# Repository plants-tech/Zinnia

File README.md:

# ZinniaGCC

fork of a fork of phob 2.x (Phob 2.x Official -> PhloraGCC -> ZinniaGCC)

RIP Jack Plants 

## Changes

* USB D+/D- Pad Alignment with [Model U GCC v2](https://github.com/plants-tech/Model-U-GCC-V2)
* Left Z implementation via its own pin; GPIO12
* Start Pad edit; now in style of D-Pad 
* B3f tactile switch thru-holes on ABXY pads
* Omron D2LS alignment thru-holes on ABXY pads (experimental)
* Revision of both Analog and C-Stick footprints; removal of t1/t2 thru-holes, conversion of t3 screw-holes from copper-lined pads to non-conductive thru-holes (screws work more effectively, stickbox "wobble" eliminated slightly)

## Images

### Front

### Back

## License

[CERN_OHL_S_v2](https://ohwr.org/cern_ohl_s_v2.txt)

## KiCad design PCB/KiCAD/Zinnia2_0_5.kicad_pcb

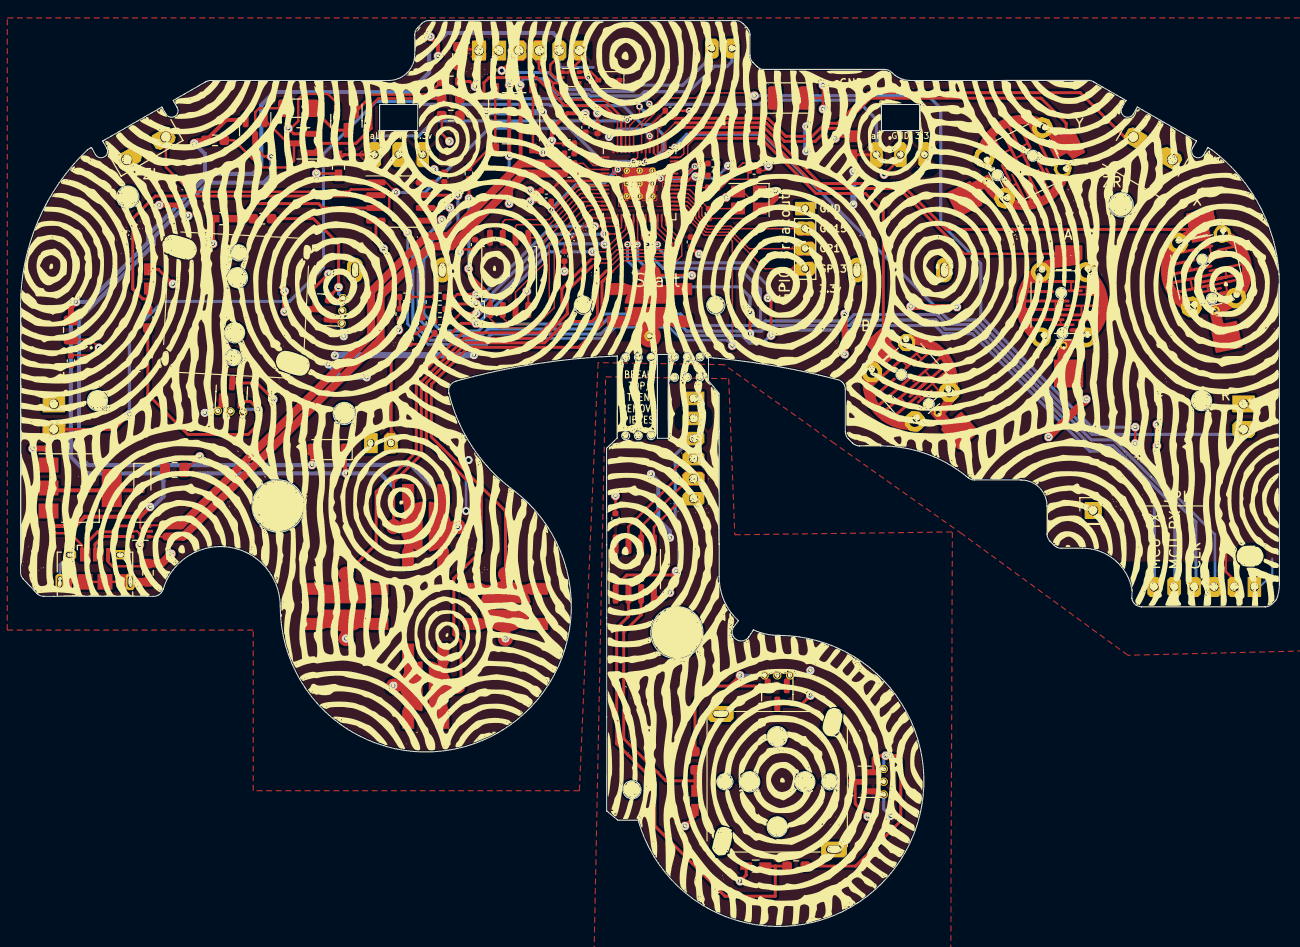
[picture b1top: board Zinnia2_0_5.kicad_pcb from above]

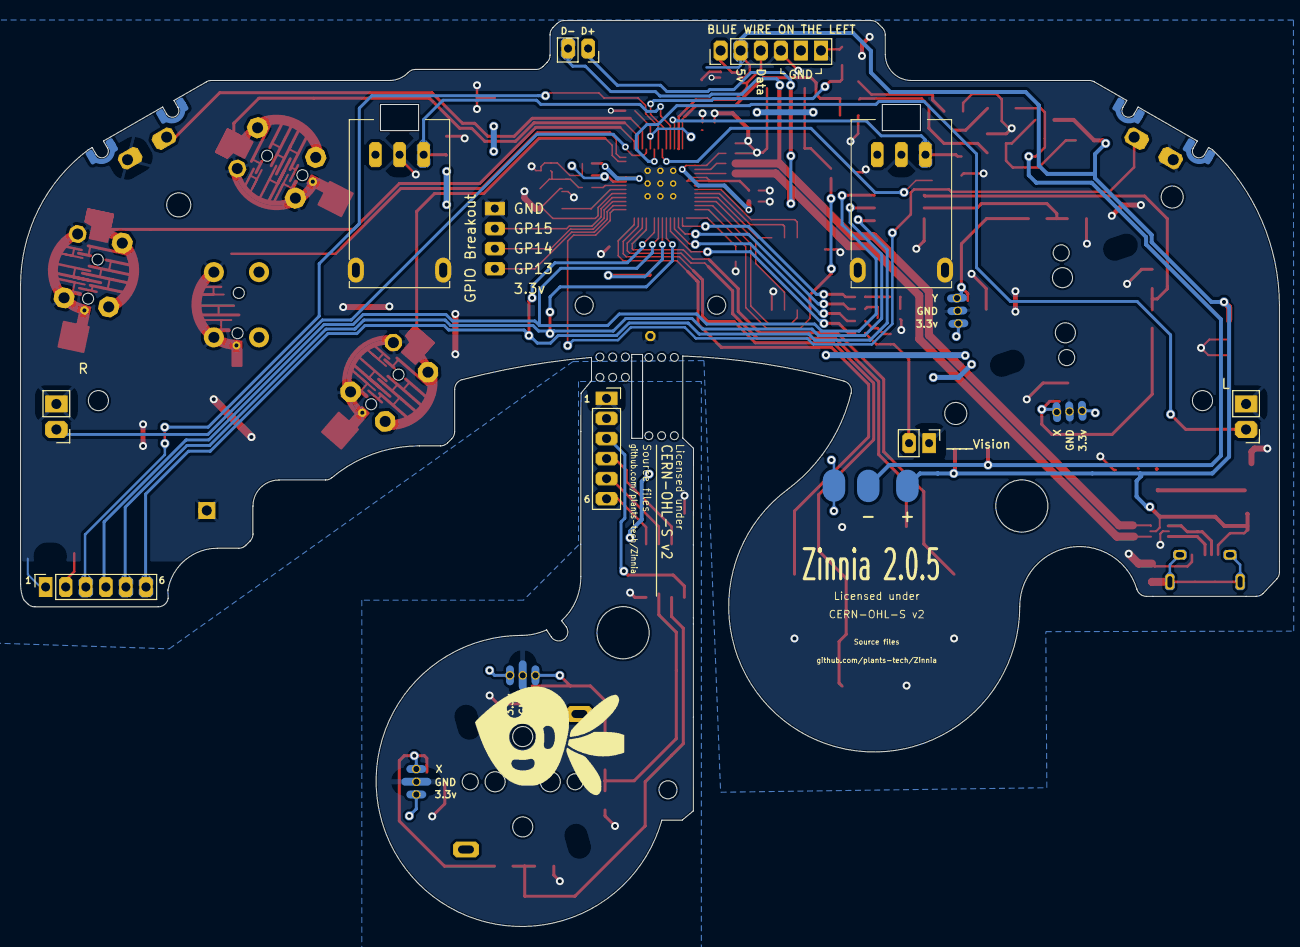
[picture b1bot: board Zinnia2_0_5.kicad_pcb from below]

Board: 2 copper layers, 125.4 x 90.3 mm, 110 parts (9 on the bottom side), 77 nets.

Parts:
C1: 47u; CP_EIA-3528-12_Kemet-T
C3, C4, C5, C6, C7, C8: 0.047u; C_0603_HandSoldering
C14, C15: 27p; C_0402_1005Metric
C16, C18: 10u; C_0805_2012Metric
C17, C19, C20, C22, C24, C25, C26, C27, C28, C29, C30, C31, C32: 100n; C_0402_1005Metric
C21, C23: 1u; C_0402_1005Metric
D1, D5: CUS10S30,H3F; D_SOD-323
D2: M7C; D_SOD-123
F1: Fuse; Fuse_1206_3216Metric
H1: 5.2mm; MountingHole_5.2mm
H2: Slot
H3, H4: 2mm; MountingHole_2.0mm
H5, H6: 1.8mm; MountingHole_1.8mm
H7: 2.4mm; MountingHole_2.4mm
H8, H9: 2.2mm; MountingHole_2.2mm
H10: MountingHole; MountingHole_1.8mm
H11: MountingHole; MountingHole_5.2mm
H12, H13: MountingHole; MountingHole_2.0mm
H14: MouseBite; breakaway-mousebites-double-v2-small
H15: MouseBite; breakaway-mousebites-double-v2-large
J1: Conn_01x06_Female; GCC_Header_Straight_1x06_Pitch2.00mm
J2, J11: Conn_01x02; PinHeader_1x02_P2.00mm_Vertical
J4: Conn_01x01; PinHeader_1x01_P2.54mm_Vertical
J5: Rumble; rumble_pins
J6: PinSocket_1x04_P2.00mm_Vertical
J9: USB_B_Micro; USB_Micro-B_Amphenol_10118194_Horizontal
J14, J15: Conn_01x06; PinSocket_1x06_P2.00mm_Vertical
Q1, Q3: Q_NMOS_GSD; SOT-23
Q2: Q_PMOS_GDS; SOT-23
R1, R2, R7, R8, R9: 180; R_0402_1005Metric
R3, R4, R5, R6: 2k; R_0603_1608Metric_Pad0.98x0.95mm_HandSolder
R10, R19, R24, R25: 316; R_0402_1005Metric
R11, R12: 100R; R_0603_1608Metric_Pad0.98x0.95mm_HandSolder
R13, R14, R15: 10k; R_0603_1608Metric_Pad0.98x0.95mm_HandSolder
R16, R18: 1k; R_0402_1005Metric
R17: 100k; R_0603_1608Metric_Pad0.98x0.95mm_HandSolder
R20, R21: 27; R_0402_1005Metric
RV1, RV2: R_POT_MountingPin; f
S1: BOOTSEL; SW_TS-1187A-B-A-B
SW1: A; ABXY_Contact_Omron_Switch_b3F_v2
SW2: B; ABXY_Contact_Omron_Switch_b3F_v2
SW3: X; ABXY_Contact_Omron_Switch_b3F_v2
SW4: Y; ABXY_Contact_Omron_Switch_b3F_v2
SW5: Start; Dpad_Contact_TL3315NF_2
SW6: L; Pin_Header_Straight_1x02_Pitch2.54mm
SW7: R; Pin_Header_Straight_1x02_Pitch2.54mm
SW8: Z; Z_Switch_Edge_Omron
SW8L: ZL; Z_Switch_Edge_Omron
SW9: Dleft; Dpad_Contact_TL3315NF_2
SW10: Dup; Dpad_Contact_TL3315NF_2
SW11: Dright; Dpad_Contact_TL3315NF_2
SW12: Ddown; Dpad_Contact_TL3315NF_2
U1, U3: MCP3002; SOIC-8_3.9x4.9mm_P1.27mm
U2: Stickbox_Assembly_Main; GCC_Stickbox_Hall_Only
U4, U9, U10, U11: DRV5055Z3QDBZT; SOT-23
U5: Stickbox_Assembly_CStick; GCC_Stickbox_Hall_Only
U6: AMS1117-3.3; SOT-223-3_TabPin2
U7: W25Q128JVS; SOIC-8_5.23x5.23mm_P1.27mm
U8: RP2040; RP2040-QFN-56
U12, U13: USBLC6-2P6; SOT-666
Y1: Crystal_GND24; Crystal_SMD_3225-4Pin_3.2x2.5mm

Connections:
+1V1: C19.1, C20.1, C21.1, U8.23 (DVDD), U8.45 (VREG_VOUT), U8.50 (DVDD)
+3V3: C1.1, C17.1, C18.1, C22.1, C23.1, C24.1, C25.1, C26.1, C27.1, C28.1, C29.1, C30.1, C31.1, D1.1 (K), D5.1 (K), J1.1, J14.2, RV1.1 (V+), RV2.1 (V+), U1.8 (VDD/VREF), U2.1 (H1XV), U2.4 (H1YV), U7.8 (VCC), U8.1 (IOVDD), U8.10 (IOVDD), U8.22 (IOVDD), U8.33 (IOVDD), U8.42 (IOVDD), U8.43 (ADC_AVDD), U8.44 (VREG_IN), U8.48 (USB_VDD), U8.49 (IOVDD), U10.1 (VCC), U11.1 (VCC), U13.4
+5V: C16.1, D2.1 (K), J1.2, J5.1, J9.1, Q2.2 (S), R13.2, U6.3 (VI), U12.5, U13.5
/A: SW1.1, U8.28 (GPIO17)
/B: SW2.1, U8.27 (GPIO16)
/Brake: R12.1, R14.2, U8.41 (GPIO29_ADC3)
/CLK: J14.4, U1.7 (CLK), U8.8 (GPIO6)
/CLK2: J15.4, U3.7 (CLK)
/CS1: U1.1 (~CS/SHDN), U8.36 (GPIO24)
/CS2: J14.3, U8.35 (GPIO23)
/CS2_2: J15.3, U3.1 (~CS/SHDN)
/C_x_filt: C5.1, R4.1, U3.2 (CH0)
/C_y_filt: C4.1, R3.1, U3.3 (CH1)
/Ddown: SW12.1, U8.13 (GPIO10)
/Din: J14.6, U1.5 (DIN), U8.9 (GPIO7)
/Din2: J15.6, U3.5 (DIN)
/Dleft: SW9.1, U8.11 (GPIO8)
/Dout: J14.5, U1.6 (DOUT), U8.6 (GPIO4)
/Dout2: J15.5, U3.6 (DOUT)
/Dright: SW11.1, U8.14 (GPIO11)
/Dup: SW10.1, U8.12 (GPIO9)
/GCC_DATA: J1.3, U8.40 (GPIO28_ADC2), U13.6
/GND_C: C4.2, C5.2, C32.2, J15.1, U3.4 (VSS), U4.3 (GND), U5.2 (H1XG), U5.5 (H1YG), U9.3 (GND)
/GPIO13: J6.4, U8.16 (GPIO13)
/GPIO14: J6.3, U8.17 (GPIO14)
/GPIO15: J6.2, U8.18 (GPIO15)
/H1XS: R6.2, U2.3 (H1XS), U10.2 (OUT)
/H1YS: R5.2, U2.6 (H1YS), U11.2 (OUT)
/H2XS: R4.2, U5.3 (H1XS), U9.2 (OUT)
/H2YS: R3.2, U4.2 (OUT), U5.6 (H1YS)
/L: SW6.1, U8.34 (GPIO22)
/Ladder1: R10.2, U8.2 (GPIO0)
/Ladder2: R19.2, U8.3 (GPIO1)
/Ladder3: R24.2, U8.4 (GPIO2)
/Ladder4: R25.2, U8.5 (GPIO3)
/Lanalog: C7.1, RV1.3 (Signal), U8.39 (GPIO27_ADC1)
/LeftZ: SW8L.2, U8.15 (GPIO12)
/QSPI_SCLK: U7.6 (CLK), U8.52 (QSPI_SCLK)
/QSPI_SD0: U7.5 (DI(IO0)), U8.53 (QSPI_SD0)
/QSPI_SD1: U7.2 (DO(IO1)), U8.55 (QSPI_SD1)
/QSPI_SD2: U7.3 (IO2), U8.54 (QSPI_SD2)
/QSPI_SD3: U7.7 (IO3), U8.51 (QSPI_SD3)
/QSPI_SS: R16.1, U7.1 (~CS), U8.56 (QSPI_SS)
/R: SW7.1, U8.32 (GPIO21)
/Ranalog: C3.1, RV2.3 (Signal), U8.38 (GPIO26_ADC0)
/Rumble: R11.1, R15.2, U8.37 (GPIO25)
/Start: SW5.1, U8.7 (GPIO5)
/Stick_x_filt: C8.1, R6.1, U1.2 (CH0)
/Stick_y_filt: C6.1, R5.1, U1.3 (CH1)
/USB_D+: J11.1, R20.1, U12.4
/USB_D-: J11.2, R21.1, U12.6
/V: J2.2, R9.1, R25.1
/X: SW3.1, U8.29 (GPIO18)
/XIN: C14.1, U8.20 (XIN), Y1.3
/XOUT: R18.1, U8.21 (XOUT)
/Y: SW4.1, U8.30 (GPIO19)
/Z: SW8.1, U8.31 (GPIO20)
/~USB_BOOT: R16.2, S1.C, S1.D
GND: C1.2, C3.2, C6.2, C7.2, C8.2, C14.2, C15.2, C16.2, C17.2, C18.2, C19.2, C20.2, C21.2, C22.2, C23.2, C24.2, C25.2, C26.2, C27.2, C28.2, C29.2, C30.2, C31.2, J1.4, J1.5, J1.6, J2.1, J4.1, J6.1, J9.5, J14.1, Q1.2 (S), Q3.2 (S), R1.2, R14.1, R15.1, R17.2, RV1.2 (GND), RV2.2 (GND), S1.A, S1.B, SW1.2, SW2.2, SW3.2, SW4.2, SW5.2, SW5.3, SW6.2, SW7.2, SW8.2, SW8L.1, SW9.2, SW10.2, SW11.2, SW12.2, U1.4 (VSS), U2.2 (H1XG), U2.5 (H1YG), U6.1 (GND), U7.4 (GND), U8.19 (TESTEN), U8.57 (GND), U10.3 (GND), U11.3 (GND), U12.2, U13.2, Y1.2, Y1.4
unnamed: C15.1, R18.2, Y1.1
unnamed: D1.2 (A), U6.2 (VO)
unnamed: D2.2 (A), F1.1, J5.2, Q2.3 (D)
unnamed: D5.2 (A), U13.3
unnamed: F1.2, Q3.3 (D)
unnamed: J9.6, R17.1
unnamed: Q1.1 (G), R12.2
unnamed: Q1.3 (D), Q2.1 (G), R13.1
unnamed: Q3.1 (G), R11.2
unnamed: R1.1, R2.2
unnamed: R2.1, R7.2, R10.1
unnamed: R7.1, R8.2, R19.1
unnamed: R20.2, U8.47 (USB_DP)
unnamed: R21.2, U8.46 (USB_DM)
unnamed: R8.1, R9.2, R24.1
USB_D+_Raw: J9.3, U12.3
USB_D-_Raw: J9.2, U12.1
VCC: C32.1, J15.2, U3.8 (VDD/VREF), U4.1 (VCC), U5.1 (H1XV), U5.4 (H1YV), U9.1 (VCC)

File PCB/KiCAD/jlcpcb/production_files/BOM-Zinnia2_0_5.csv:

Comment,Designator,Footprint,LCSC
1k,"R16,R18",R_0402_1005Metric,C11702
USB_B_Micro,J9,USB_Micro-B_Amphenol_10118194_Horizontal,C132563
27,"R20,R21",R_0402_1005Metric,C138021
"CUS10S30,H3F","D1,D5",D_SOD-323,C146335
Q_PMOS_GDS,Q2,SOT-23,C15127
100n,"C17,C19,C20,C22,C24,C25,C26,C27,C28,C29,C30,C31,C32",C_0402_1005Metric,C1525
27p,"C14,C15",C_0402_1005Metric,C1557
10u,"C16,C18",C_0805_2012Metric,C15850
316,"R10,R19,R24,R25",R_0402_1005Metric,C159037
0.047u,"C3,C4,C5,C6,C7,C8",C_0603_HandSoldering,C1622
RP2040,U8,RP2040-QFN-56,C2040
Q_NMOS_GSD,"Q1,Q3",SOT-23,C20917
100R,"R11,R12",R_0603_1608Metric_Pad0.98x0.95mm_HandSolder,C22775
2k,"R3,R4,R5,R6",R_0603_1608Metric_Pad0.98x0.95mm_HandSolder,C22975
100k,R17,R_0603_1608Metric_Pad0.98x0.95mm_HandSolder,C25803
10k,"R13,R14,R15",R_0603_1608Metric_Pad0.98x0.95mm_HandSolder,C25804
DRV5055A2xDBZxQ1,"U10,U11,U4,U9",SOT-23,C266131
BOOTSEL,S1,SW_TS-1187A-B-A-B,C318884
180,"R1,R2,R7,R8,R9",R_0402_1005Metric,C38941
Crystal_GND24,Y1,Crystal_SMD_3225-4Pin_3.2x2.5mm,C403945
1u,"C21,C23",C_0402_1005Metric,C52923
MCP3002,"U1,U3",SOIC-8_3.9x4.9mm_P1.27mm,C56997
AMS1117-3.3,U6,SOT-223-3_TabPin2,C6186
Fuse,F1,Fuse_1206_3216Metric,C69680
M7C,D2,D_SOD-123,C8598
W25Q128JVS,U7,SOIC-8_5.23x5.23mm_P1.27mm,C97521

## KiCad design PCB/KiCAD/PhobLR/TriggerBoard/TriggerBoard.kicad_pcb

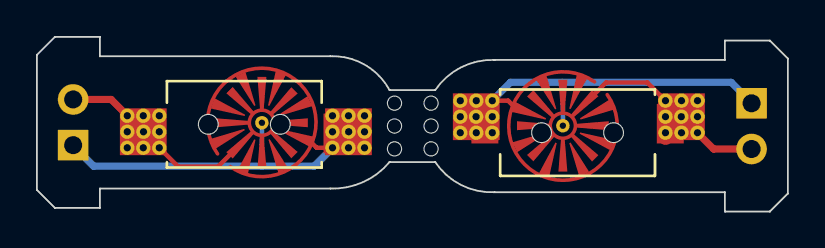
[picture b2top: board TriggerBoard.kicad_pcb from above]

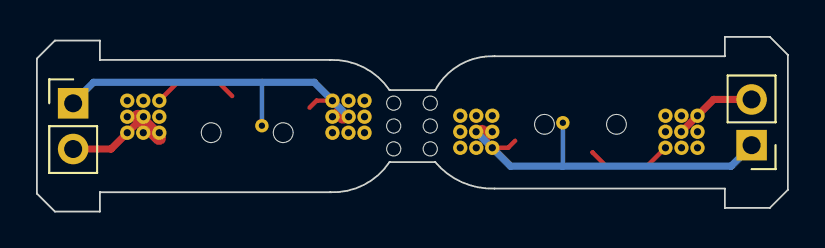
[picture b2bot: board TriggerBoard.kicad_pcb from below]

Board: 2 copper layers, 41.7 x 9.7 mm, 5 parts (2 on the bottom side), 4 nets.

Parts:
H2: MouseBiteRA; breakaway-mousebites-double
J1: L; Pin_Header_Straight_1x02_Pitch2.54mm
J2: R; Pin_Header_Straight_1x02_Pitch2.54mm
SW1: L; Trigger_Contact_Big
SW2: R; Trigger_Contact_Big

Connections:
unnamed: J1.1, SW1.1
unnamed: J1.2, SW1.2
unnamed: J2.1, SW2.1
unnamed: J2.2, SW2.2

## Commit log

2023-04-27 gittem
2023-04-27 license_n_ignore
2023-04-27 cleaning house
2023-04-27 house part 2
    cleany
2023-04-28 pushy
    fixed thru holes
2023-04-28 MOUSEY THRU HOLE
    U ALREADY KNOW
2023-04-28 B3f pad test
2023-04-29 Pad Updated
2023-05-04 removed t2 support
2023-05-04 touch up/finish job on t3-screw-thru-holes
2023-05-22 Doing usbc stuff (unfinished)
    Removed Cfan silkscreen
    added silkscreen
    added usbc (unfinished)
    need to look for different usbc
2023-05-30 2.0.5 pcb complete
2023-05-30 2.0.5 actually complete lol
2023-05-30 2.0.5 release ready
2023-05-30 clean
2023-06-02 Updated Prod files
    Fixed D2
2023-06-03 Revert "Updated Prod files"
    This reverts commit 61c3d7e021a4cafdf2df5ba8c0fc9619fe45cfe2.
2023-06-03 cleaned up folders
2023-06-03 revised, ready 2 go
2023-06-15 cringe updates
2023-06-15 2.0.5 final
2023-06-16 2.0.5 plus actually good for real
2023-06-16 image update :)
2023-07-03 elecrow order info (not complete yet)
2023-07-22 Fixed and updated
    Fixed BOM
    Fixed gerber for elecrow
    added Plant logo
    changed silkscreen for elecrow
    removed PTH for trigger mounting
    This should be the last update for now.
2023-07-27 Updated C16
    Double checked bom after regenerating gerbers
    moved C16 slightly to left for clearance
2023-07-27 Added Silkscreen variant
    Added flower variant silkscreen
2023-08-04 added 3.3v pad on back
2023-08-04 Updated for Z3 test
2025-03-06 New PC
    Untested

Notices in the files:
PCB/KiCAD/Zinnia2_0_5.kicad_pcb:
Licensed under
B.SilkS
